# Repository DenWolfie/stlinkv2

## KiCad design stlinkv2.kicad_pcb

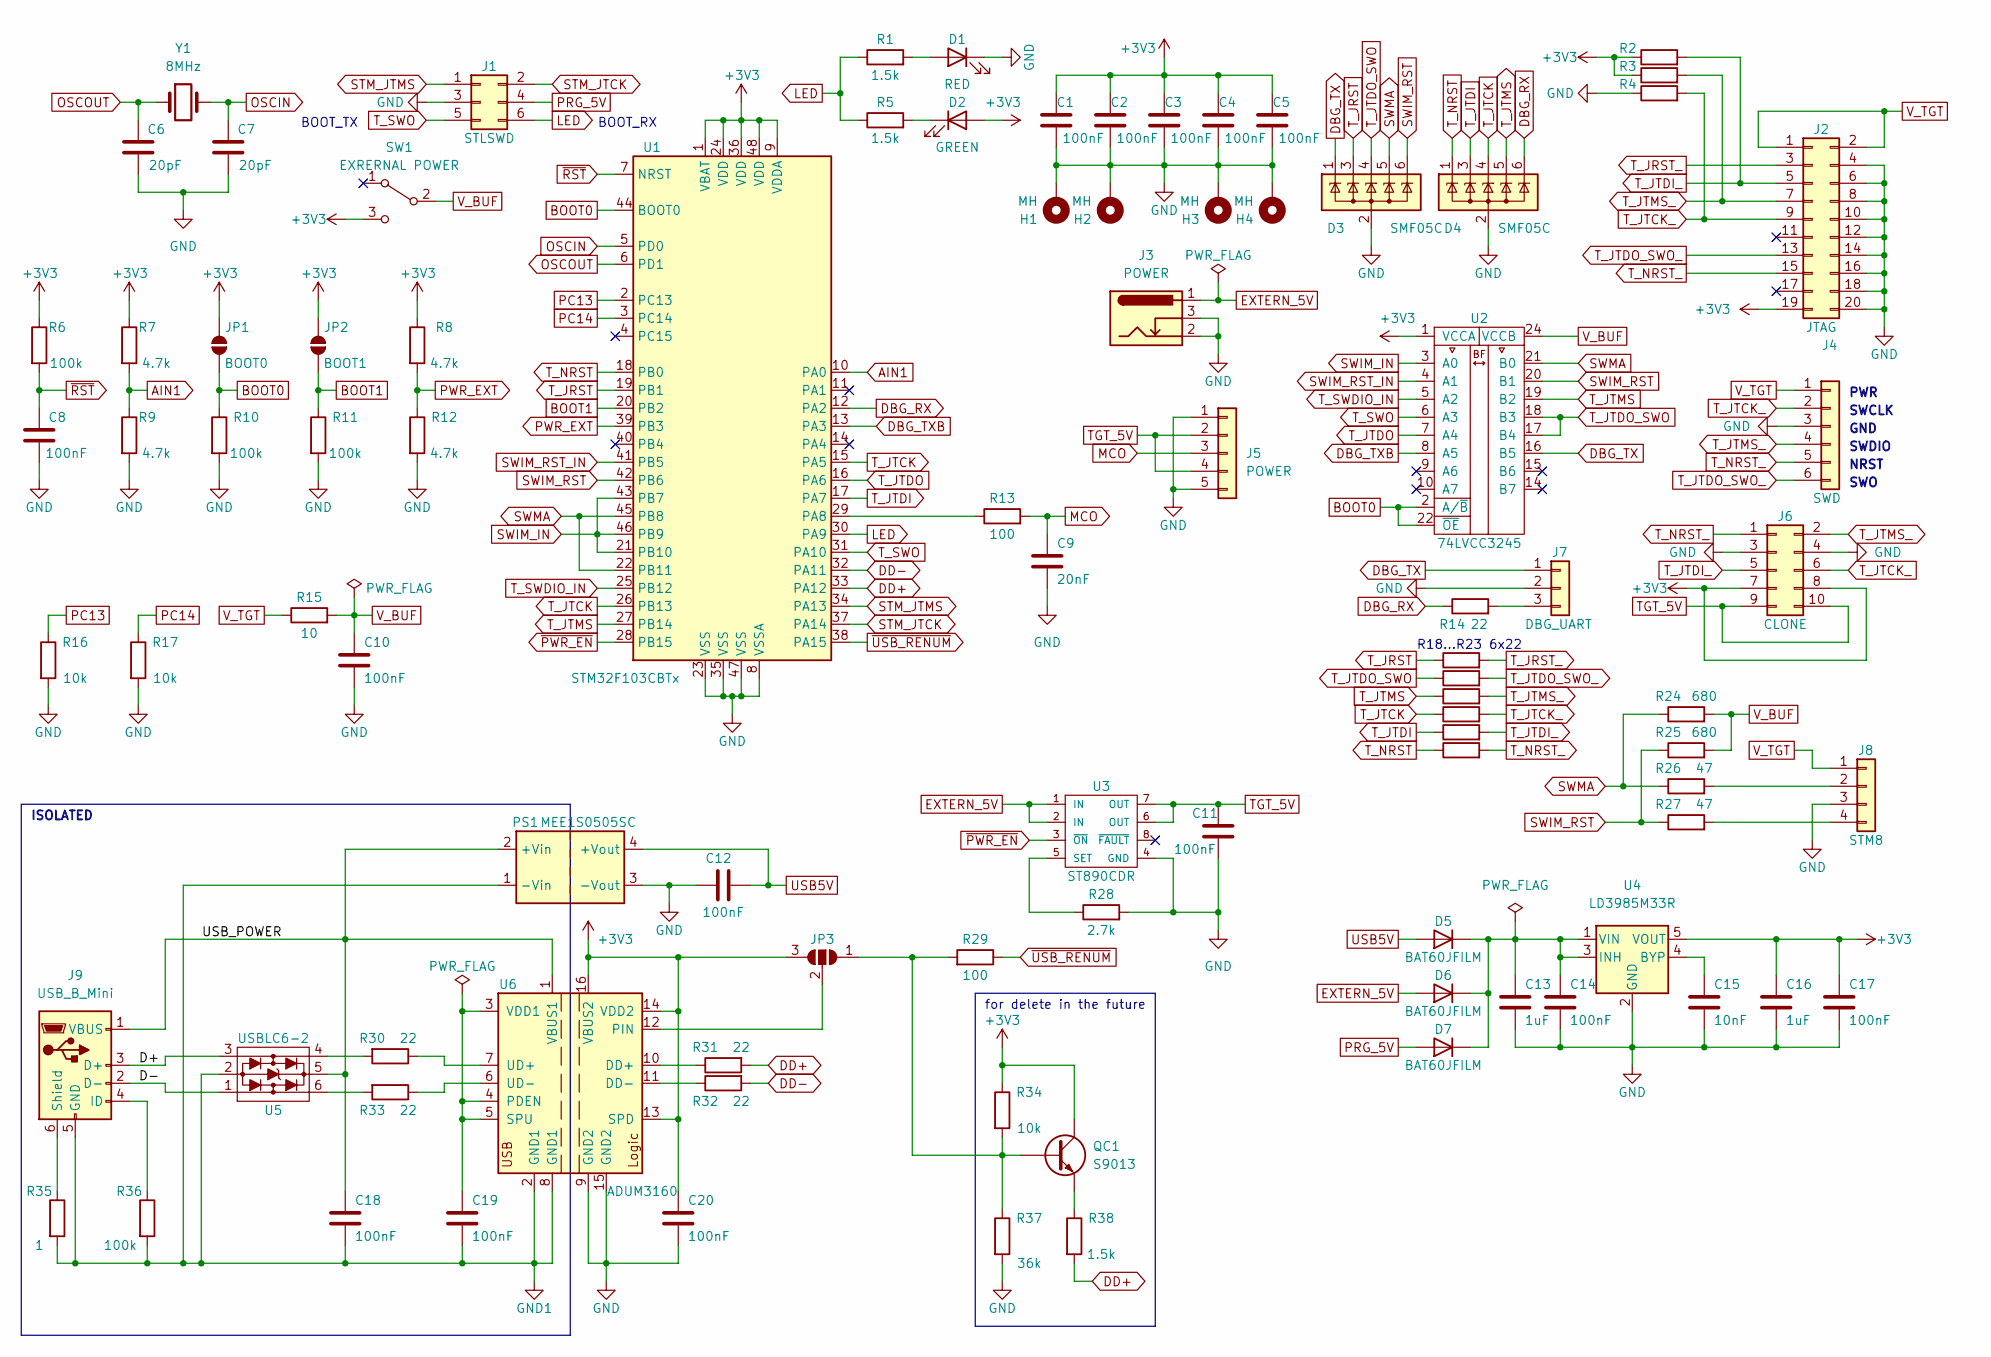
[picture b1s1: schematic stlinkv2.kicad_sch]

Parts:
C1, C2, C3, C4, C5, C8, C10, C11, C12, C14, C17, C18, C19, C20: 100nF; C_0805_2012Metric
C6, C7: 20pF; C_0805_2012Metric
C9: 20nF; C_0805_2012Metric
C13, C16: 1uF; C_0805_2012Metric
C15: 10nF; C_0805_2012Metric
D1: RED; D_0805_2012Metric
D2: GREEN; D_0805_2012Metric
D3, D4: SMF05C; SOT-363_SC-70-6
D5, D6, D7: BAT60JFILM; D_SOD-323_HandSoldering
H1, H2, H3, H4: MH; MountingHole_2.2mm_M2_ISO14580_Pad
J1: STLSWD; PinHeader_2x03_P2.54mm_Vertical
J2: JTAG; IDC-Header_2x10_P2.54mm_Vertical
J3: POWER; 3.5mm power
J4: SWD; PinHeader_1x06_P2.54mm_Vertical
J5: POWER; PinHeader_1x05_P2.54mm_Vertical
J6: CLONE; IDC-Header_2x05_P2.54mm_Vertical
J7: DBG_UART; PinHeader_1x03_P2.54mm_Vertical
J8: STM8; PinHeader_1x04_P2.54mm_Vertical
J9: USB_B_Mini; USB_Mini-B_Wuerth_65100516121_Horizontal
JP1: BOOT0; SolderJumper-2_P1.3mm_Open_TrianglePad1.0x1.5mm
JP2: BOOT1; SolderJumper-2_P1.3mm_Open_TrianglePad1.0x1.5mm
JP3: USB CONTROL; SolderJumper-3_P1.3mm_Open_RoundedPad1.0x1.5mm
PS1: MEE1S0505SC; Converter_DCDC_Murata_MEE1SxxxxSC_THT
QC1: S9013; SOT-23_Handsoldering
R1, R5, R38: 1.5k; R_0805_2012Metric
R2, R3, R4, R16, R17, R34: 10k; R_0805_2012Metric
R6, R10, R11, R36: 100k; R_0805_2012Metric
R7, R8, R9, R12: 4.7k; R_0805_2012Metric
R13, R29: 100; R_0805_2012Metric
R14, R18, R19, R20, R21, R22, R23, R30, R31, R32, R33: 22; R_0805_2012Metric
R15: 10; R_0805_2012Metric
R24, R25: 680; R_0805_2012Metric
R26, R27: 47; R_0805_2012Metric
R28: 2.7k; R_0805_2012Metric
R35: 1; R_0805_2012Metric
R37: 36k; R_0805_2012Metric
SW1: EXRERNAL POWER; SW_SPDT_PCM12
U1: STM32F103CBTx; LQFP-48_7x7mm_P0.5mm
U2: 74LVCC3245; TSSOP-24_4.4x7.8mm_P0.65mm
U3: ST890CDR; SO-8_3.9x4.9mm_P1.27mm
U4: LD3985M33R; SOT-23-5
U5: USBLC6-2; SOT-23-6_Handsoldering
U6: ADUM3160; SOIC-16W_7.5x10.3mm_P1.27mm
Y1: 8MHz; Crystal_HC49-4H_Vertical

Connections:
+3V3: C1.1, C2.1, C3.1, C4.1, C5.1, C16.1, C17.1, C20.1, D2.2 (A), J2.19, J6.7, J6.8, JP1.1 (A), JP2.1 (A), JP3.3 (B), QC1.3 (C), R2.1, R3.1, R6.1, R7.1, R8.1, R34.1, SW1.3 (C), U1.1 (VBAT), U1.9 (VDDA), U1.24 (VDD), U1.36 (VDD), U1.48 (VDD), U2.1 (VCCA), U4.5 (VOUT), U6.13 (SPD), U6.14 (VDD2), U6.16 (VBUS2)
/D+: J9.3 (D+), U5.3
/D-: J9.2 (D-), U5.1
/USB_POWER: C18.1, J9.1 (VBUS), PS1.2 (+Vin), U5.5, U6.1 (VBUS1)
AIN1: R7.2, R9.1, U1.10 (PA0)
BOOT0: JP1.2 (B), R10.1, U1.44 (BOOT0), U2.2 (A/~B), U2.22 (~OE)
BOOT1: JP2.2 (B), R11.1, U1.20 (PB2)
DBG_RX: D4.6 (K), R14.1, U1.12 (PA2)
DBG_TX: D3.1 (K), J7.1, U2.16 (B5)
DBG_TXB: U1.13 (PA3), U2.8 (A5)
DD+: R31.2, R38.2, U1.33 (PA12)
DD-: R32.2, U1.32 (PA11)
EXTERN_5V: D6.2 (A), J3.1, U3.1 (IN), U3.2 (IN)
GND: C1.2, C2.2, C3.2, C4.2, C5.2, C6.2, C7.2, C8.2, C9.2, C10.2, C11.2, C12.1, C13.2, C14.2, C15.2, C16.2, C17.2, C20.2, D1.1 (K), D3.2 (A), D4.2 (A), H1.1, H2.1, H3.1, H4.1, J1.3, J2.4, J2.6, J2.8, J2.10, J2.12, J2.14, J2.16, J2.18, J2.20, J3.2, J3.3, J4.3, J5.1, J5.5, J6.3, J6.4, J7.2, J8.3, PS1.3 (-Vout), R4.1, R9.2, R10.2, R11.2, R12.2, R16.2, R17.2, R28.2, R37.2, U1.8 (VSSA), U1.23 (VSS), U1.35 (VSS), U1.47 (VSS), U2.11 (GND), U2.12 (GND), U2.13 (GND), U3.4 (GND), U4.2 (GND), U6.9 (GND2), U6.15 (GND2)
GND1: C18.2, C19.2, J9.5 (GND), PS1.1 (-Vin), R35.2, R36.2, U5.2, U6.2 (GND1), U6.8 (GND1)
LED: J1.6, R1.1, R5.1, U1.30 (PA9)
MCO: C9.1, J5.3, R13.2
unnamed: C13.1, C14.1, D5.1 (K), D6.1 (K), D7.1 (K), U4.1 (VIN), U4.3 (INH)
unnamed: C15.1, U4.4 (BYP)
unnamed: C19.1, U6.3 (VDD1), U6.4 (PDEN), U6.5 (SPU)
unnamed: D1.2 (A), R1.2
unnamed: D2.1 (K), R5.2
unnamed: J7.3, R14.2
unnamed: J8.2, R26.2
unnamed: J8.4, R27.2
unnamed: J9.4 (ID), R36.1
unnamed: J9.6 (Shield), R35.1
unnamed: JP3.1 (A), QC1.1 (B), R29.2, R34.2, R37.1
unnamed: JP3.2 (C), U6.12 (PIN)
unnamed: QC1.2 (E), R38.1
unnamed: R13.1, U1.29 (PA8)
unnamed: R28.1, U3.5 (SET)
unnamed: R30.1, U6.7 (UD+)
unnamed: R30.2, U5.4
unnamed: R31.1, U6.10 (DD+)
unnamed: R32.1, U6.11 (DD-)
unnamed: R33.1, U6.6 (UD-)
unnamed: R33.2, U5.6
OSCIN: C7.1, U1.5 (PD0), Y1.2
OSCOUT: C6.1, U1.6 (PD1), Y1.1
PC13: R16.1, U1.2 (PC13)
PC14: R17.1, U1.3 (PC14)
PRG_5V: D7.2 (A), J1.4
PWR_EXT: R8.2, R12.1, U1.39 (PB3)
STM_JTCK: J1.2, U1.37 (PA14)
STM_JTMS: J1.1, U1.34 (PA13)
SWIM_IN: U1.21 (PB10), U1.43 (PB7), U1.46 (PB9), U2.3 (A0)
SWIM_RST: D3.6 (K), R25.1, R27.1, U1.42 (PB6), U2.20 (B1)
SWIM_RST_IN: U1.41 (PB5), U2.4 (A1)
SWMA: D3.5 (K), R24.1, R26.1, U1.22 (PB11), U1.45 (PB8), U2.21 (B0)
TGT_5V: C11.1, J5.2, J5.4, J6.9, J6.10, U3.6 (OUT), U3.7 (OUT)
T_JRST: D3.3 (K), R18.1, U1.19 (PB1)
T_JRST_: J2.3, R18.2
T_JTCK: D4.4 (K), R21.1, U1.15 (PA5), U1.26 (PB13)
T_JTCK_: J2.9, J4.2, J6.6, R4.2, R21.2
T_JTDI: D4.3 (K), R22.1, U1.17 (PA7)
T_JTDI_: J2.5, J6.5, R2.2, R22.2
T_JTDO: U1.16 (PA6), U2.7 (A4)
T_JTDO_SWO: D3.4 (K), R19.1, U2.17 (B4), U2.18 (B3)
T_JTDO_SWO_: J2.13, J4.6, R19.2
T_JTMS: D4.5 (K), R20.1, U1.27 (PB14), U2.19 (B2)
T_JTMS_: J2.7, J4.4, J6.2, R3.2, R20.2
T_NRST: D4.1 (K), R23.1, U1.18 (PB0)
T_NRST_: J2.15, J4.5, J6.1, R23.2
T_SWDIO_IN: U1.25 (PB12), U2.5 (A2)
T_SWO: J1.5, U1.31 (PA10), U2.6 (A3)
USB5V: C12.2, D5.2 (A), PS1.4 (+Vout)
V_BUF: C10.1, R15.2, R24.2, R25.2, SW1.2 (B), U2.24 (VCCB)
V_TGT: J2.1, J2.2, J4.1, J8.1, R15.1
~PWR_EN: U1.28 (PB15), U3.3 (~ON)
~RST: C8.1, R6.2, U1.7 (NRST)
~USB_RENUM: R29.1, U1.38 (PA15)

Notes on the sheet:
BOOT_RX
SWCLK
GND
NRST
R18...R23 6x22
SWDIO
SWO
for delete in the future
PWR
ISOLATED
BOOT_TX

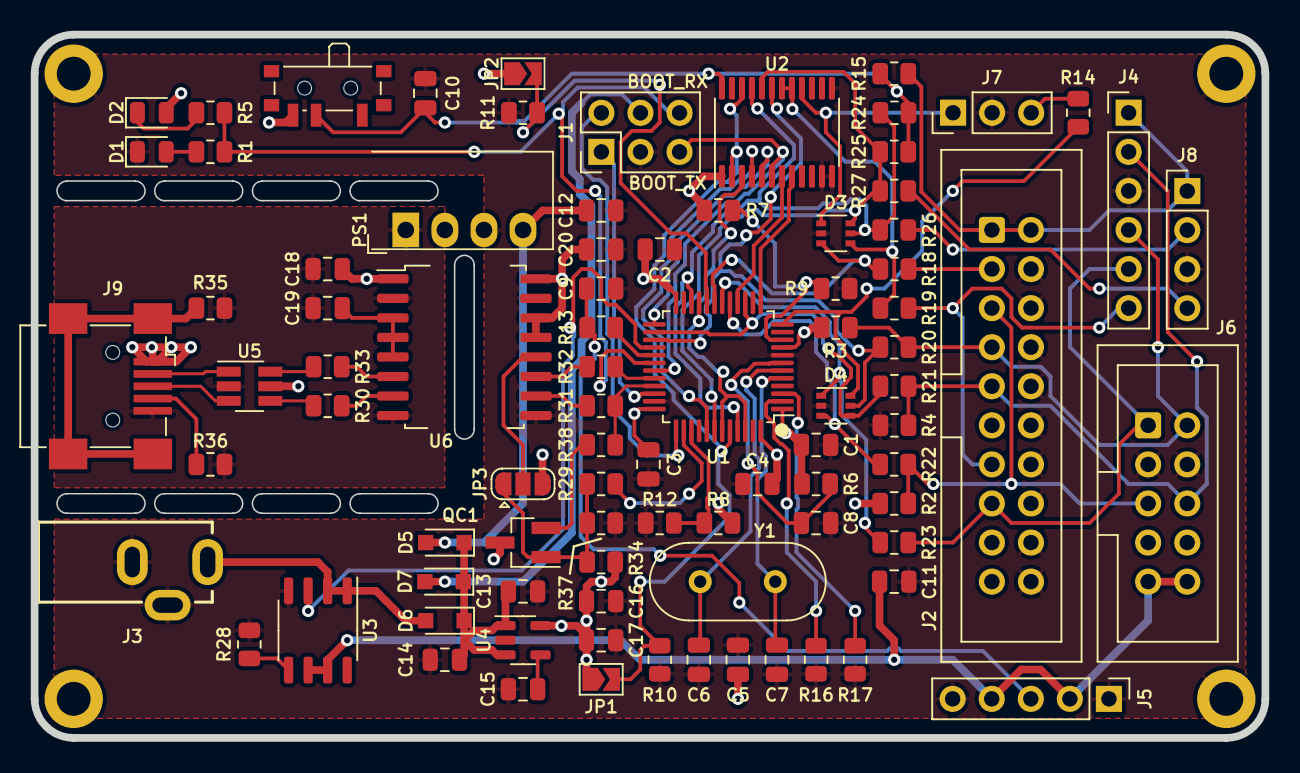
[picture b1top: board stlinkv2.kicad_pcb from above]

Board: 2 copper layers, 80.0 x 45.7 mm, 91 parts (0 on the bottom side), 72 nets.
